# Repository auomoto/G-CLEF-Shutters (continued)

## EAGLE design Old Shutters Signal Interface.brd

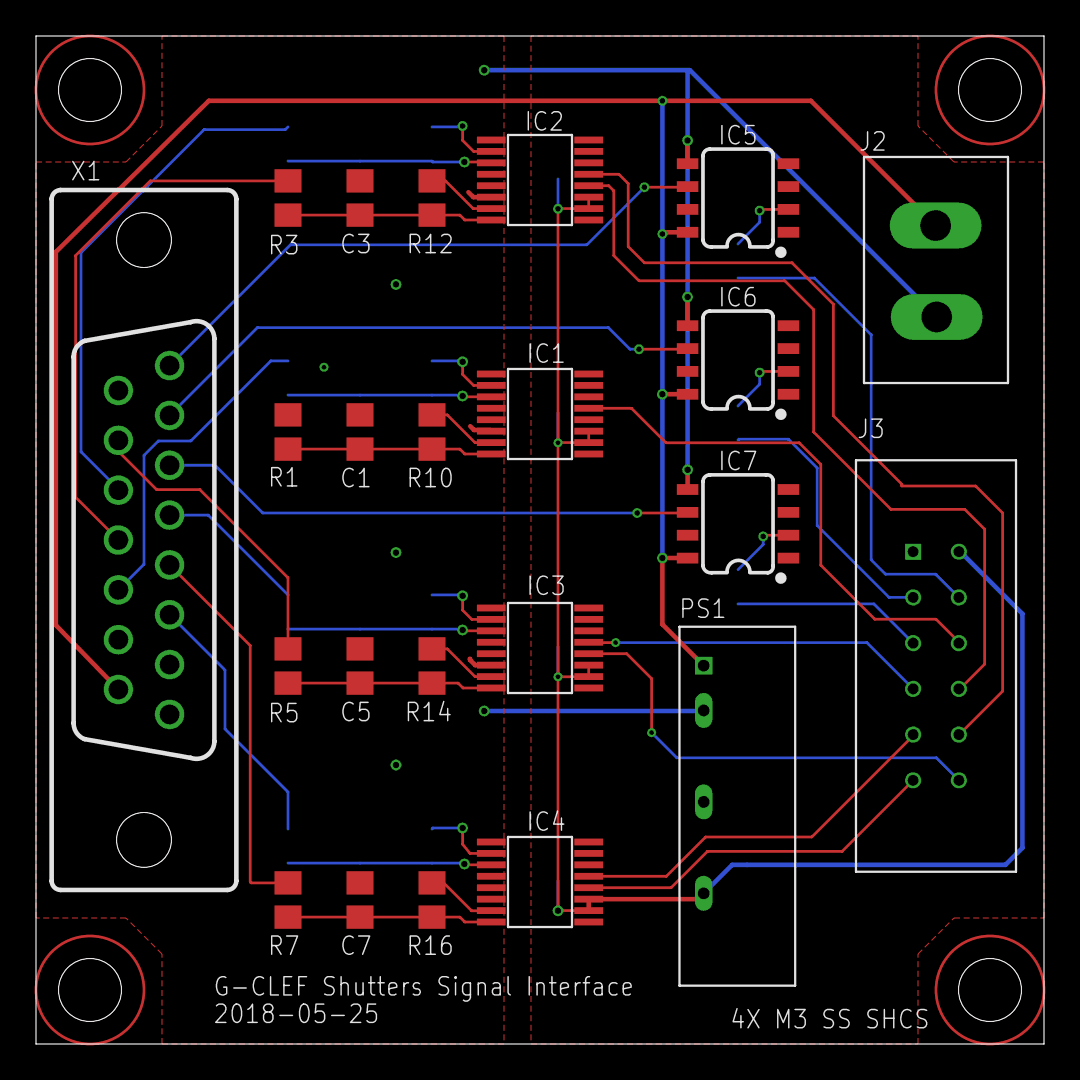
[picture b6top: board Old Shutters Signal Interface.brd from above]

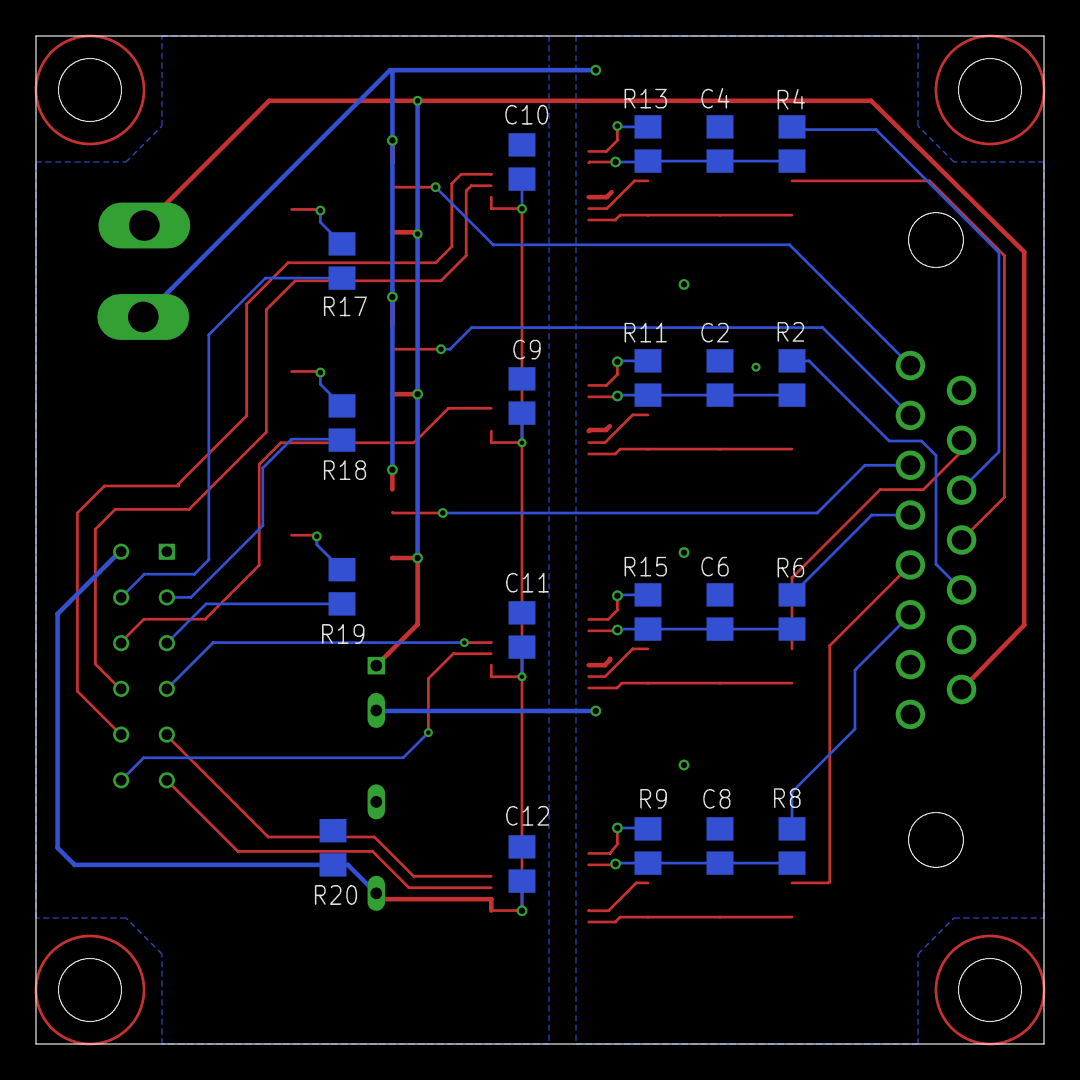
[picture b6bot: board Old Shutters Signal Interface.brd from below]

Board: 2 copper layers, 56.0 x 56.0 mm, 43 parts (20 on the bottom side), 43 nets.

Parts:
C1, C2, C3, C4, C5, C6, C7, C8: 10nF; C0805
C9, C10, C11, C12: 0.1uF; C0805
IC1, IC2, IC3, IC4: ISO1212
IC5, IC6, IC7: SI8710; SO08
J2: MSTBVA
J3: SAMTEC12
PS1: MER1S2405SC; MER1
R1, R2, R3, R4, R5, R6, R7, R8: 1K; R0805
R9, R10, R11, R12, R13, R14, R15, R16: 562R; R0805
R17, R18, R19: R0805
R20: 249R; R0805
X1: D-SUB15-H2R15ST; H2R15ST

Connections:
5V: C9.1, C10.1, C11.1, C12.1, IC1.2, IC1.3, IC2.2, IC2.3, IC3.2, IC3.3, IC4.2, IC4.3, J3.2, PS1.6, R20.1
24V: IC5.8, IC6.8, IC7.8, J2.2, PS1.1, X1.9
A$0: R3.1, X1.12
A$1: R4.1, X1.13
A$2: R5.1, X1.14
D$0: R8.1, X1.3
D$1: R7.1, X1.4
D$2: R6.1, X1.5
GND: C9.2, C10.2, C11.2, C12.2, IC1.1, IC1.8, IC2.1, IC2.8, IC3.1, IC3.8, IC4.1, IC4.8, IC5.3, IC6.3, IC7.3, J3.1, PS1.4, R20.2
GND-ISO: C1.2, C2.2, C3.2, C4.2, C5.2, C6.2, C7.2, C8.2, IC1.9, IC1.14, IC2.9, IC2.14, IC3.9, IC3.14, IC4.9, IC4.14, IC5.5, IC6.5, IC7.5, J2.1, PS1.2, R1.1, X1.1
unnamed: IC5.2, R17.2
unnamed: C1.1, IC1.16, R1.2, R10.1
unnamed: IC7.6, X1.6
unnamed: IC1.15, R10.2
unnamed: IC1.10, R11.2
unnamed: C2.1, IC1.11, R2.2, R11.1
unnamed: IC2.15, R12.2
unnamed: C3.1, IC2.16, R3.2, R12.1
unnamed: C4.1, IC2.11, R4.2, R13.1
unnamed: C5.1, IC3.16, R5.2, R14.1
unnamed: C6.1, IC3.11, R6.2, R15.1
unnamed: C7.1, IC4.16, R7.2, R16.1
unnamed: C8.1, IC4.11, R8.2, R9.1
unnamed: IC2.10, R13.2
unnamed: IC3.15, R14.2
unnamed: IC3.10, R15.2
unnamed: IC4.15, R16.2
unnamed: IC4.10, R9.2
unnamed: IC6.6, X1.7
unnamed: IC5.6, X1.8
unnamed: IC1.5, J3.6
unnamed: IC2.4, J3.8
unnamed: IC2.5, J3.10
unnamed: IC3.4, J3.12
unnamed: IC3.5, J3.7
unnamed: IC6.2, R18.2
unnamed: IC7.2, R19.2
unnamed: IC4.5, J3.9
unnamed: IC4.4, J3.11
S$0: J3.5, R19.1
S$1: J3.3, R18.1
S$2: J3.4, R17.1
TRIG: R2.1, X1.11
